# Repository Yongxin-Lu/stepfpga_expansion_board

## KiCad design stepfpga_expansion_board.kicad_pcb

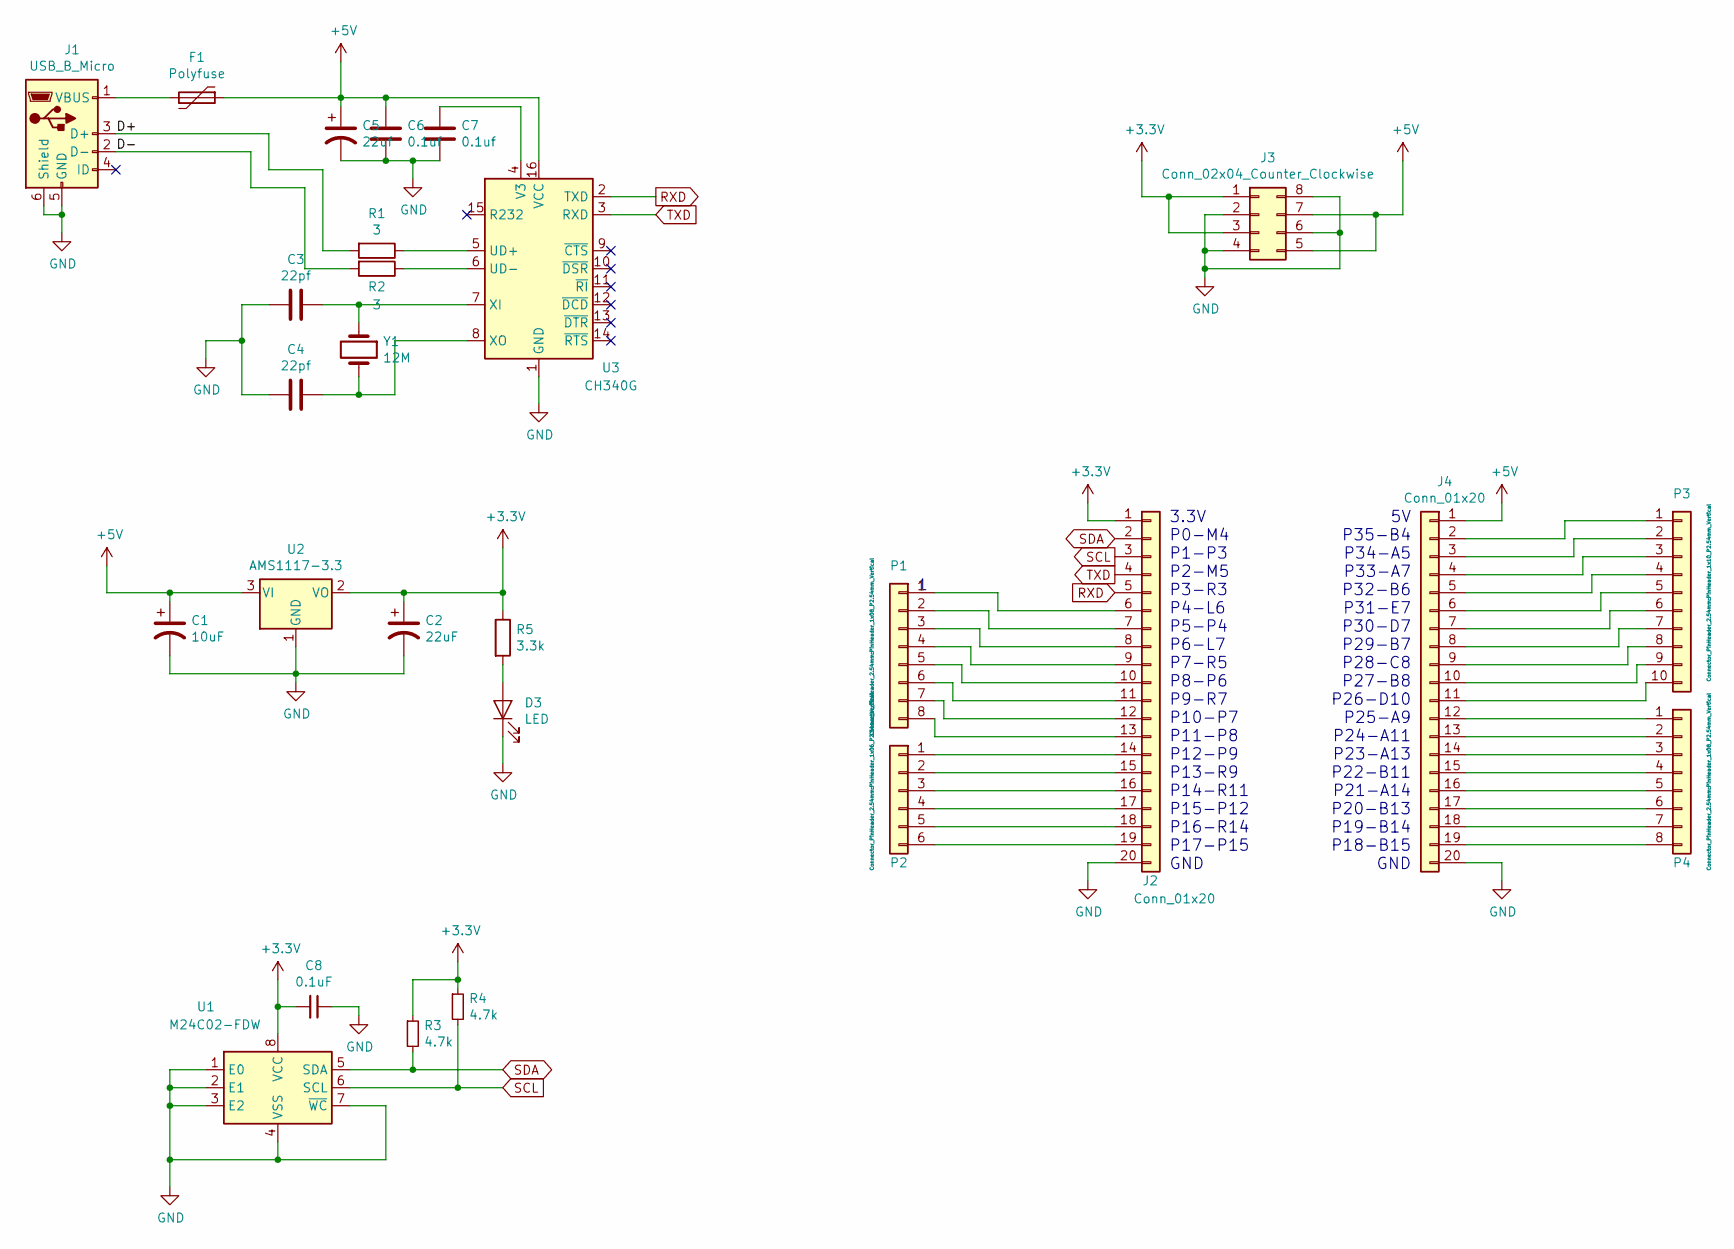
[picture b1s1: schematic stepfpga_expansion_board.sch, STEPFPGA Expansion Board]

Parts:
C1: 10uF; CP_EIA-3216-18_Kemet-A
C2: 22uF; CP_EIA-3216-18_Kemet-A
C3, C4: 22pf; C_0603_1608Metric
C5: 22uf; CP_EIA-3216-18_Kemet-A
C6, C7: 0.1uf; C_0603_1608Metric
C8: 0.1uF; C_0603_1608Metric
D3: LED; D_0603_1608Metric
F1: Polyfuse; Fuse_0805_2012Metric
J1: USB_B_Micro; USB_Micro-B_Molex_47346-0001
J2, J4: Conn_01x20; PinSocket_1x20_P2.54mm_Vertical
J3: Conn_02x04_Counter_Clockwise; PinHeader_2x04_P2.54mm_Vertical
P1: Power; PinHeader_1x08_P2.54mm_Vertical
P2: Analog; PinHeader_1x06_P2.54mm_Vertical
P3: Digital; PinHeader_1x10_P2.54mm_Vertical
P4: Digital; PinHeader_1x08_P2.54mm_Vertical
R1, R2: 3; R_0603_1608Metric
R3, R4: 4.7k; R_0603_1608Metric
R5: 3.3k; R_0603_1608Metric
U1: M24C02-FDW; TSSOP-8_4.4x3mm_P0.65mm
U2: AMS1117-3.3; SOT-223-3_TabPin2
U3: CH340G; SOIC-16_3.9x9.9mm_P1.27mm
Y1: 12M; HC49US

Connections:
+3V3: C2.1, C8.2, J2.1, J3.1, J3.3, R3.1, R4.1, R5.1, U1.8 (VCC), U2.2 (VO)
+5V: C1.1, C5.1, C6.1, F1.1, J3.5, J3.7, J4.1, U2.3 (VI), U3.16 (VCC)
/D+: J1.3 (D+), R1.2
/D-: J1.2 (D-), R2.2
GND: C1.2, C2.2, C3.2, C4.2, C5.2, C6.2, C7.2, C8.1, D3.1 (K), J1.5 (GND), J1.6 (Shield), J2.20, J3.2, J3.4, J3.6, J3.8, J4.20, U1.1 (E0), U1.2 (E1), U1.3 (E2), U1.4 (VSS), U1.7 (~WC), U2.1 (GND), U3.1 (GND)
unnamed: C3.1, U3.7 (XI), Y1.1
unnamed: C4.1, U3.8 (XO), Y1.2
unnamed: C7.1, U3.4 (V3)
unnamed: D3.2 (A), R5.2
unnamed: F1.2, J1.1 (VBUS)
unnamed: J2.6, P1.1
unnamed: J2.7, P1.2
unnamed: J2.8, P1.3
unnamed: J2.9, P1.4
unnamed: J2.10, P1.5
unnamed: J2.11, P1.6
unnamed: J2.12, P1.7
unnamed: J2.13, P1.8
unnamed: J2.14, P2.1
unnamed: J2.15, P2.2
unnamed: J2.16, P2.3
unnamed: J2.17, P2.4
unnamed: J2.18, P2.5
unnamed: J2.19, P2.6
unnamed: J4.2, P3.1
unnamed: J4.3, P3.2
unnamed: J4.4, P3.3
unnamed: J4.5, P3.4
unnamed: J4.6, P3.5
unnamed: J4.7, P3.6
unnamed: J4.8, P3.7
unnamed: J4.9, P3.8
unnamed: J4.10, P3.9
unnamed: J4.11, P3.10
unnamed: J4.12, P4.1
unnamed: J4.13, P4.2
unnamed: J4.14, P4.3
unnamed: J4.15, P4.4
unnamed: J4.16, P4.5
unnamed: J4.17, P4.6
unnamed: J4.18, P4.7
unnamed: J4.19, P4.8
unnamed: R1.1, U3.5 (UD+)
unnamed: R2.1, U3.6 (UD-)
RXD: J2.5, U3.2 (TXD)
SCL: J2.3, R4.2, U1.6 (SCL)
SDA: J2.2, R3.2, U1.5 (SDA)
TXD: J2.4, U3.3 (RXD)

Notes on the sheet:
3.3V P0-M4 P1-P3 P2-M5 P3-R3 P4-L6 P5-P4 P6-L7 P7-R5 P8-P6 P9-R7 P10-P7 P11-P8 P12-P9 P13-R9 P14-R11 P15-P12 P16-R14 P17-P15 GND
5V P35-B4 P34-A5 P33-A7 P32-B6 P31-E7 P30-D7 P29-B7 P28-C8 P27-B8 P26-D10 P25-A9 P24-A11 P23-A13 P22-B11 P21-A14 P20-B13 P19-B14 P18-B15 GND

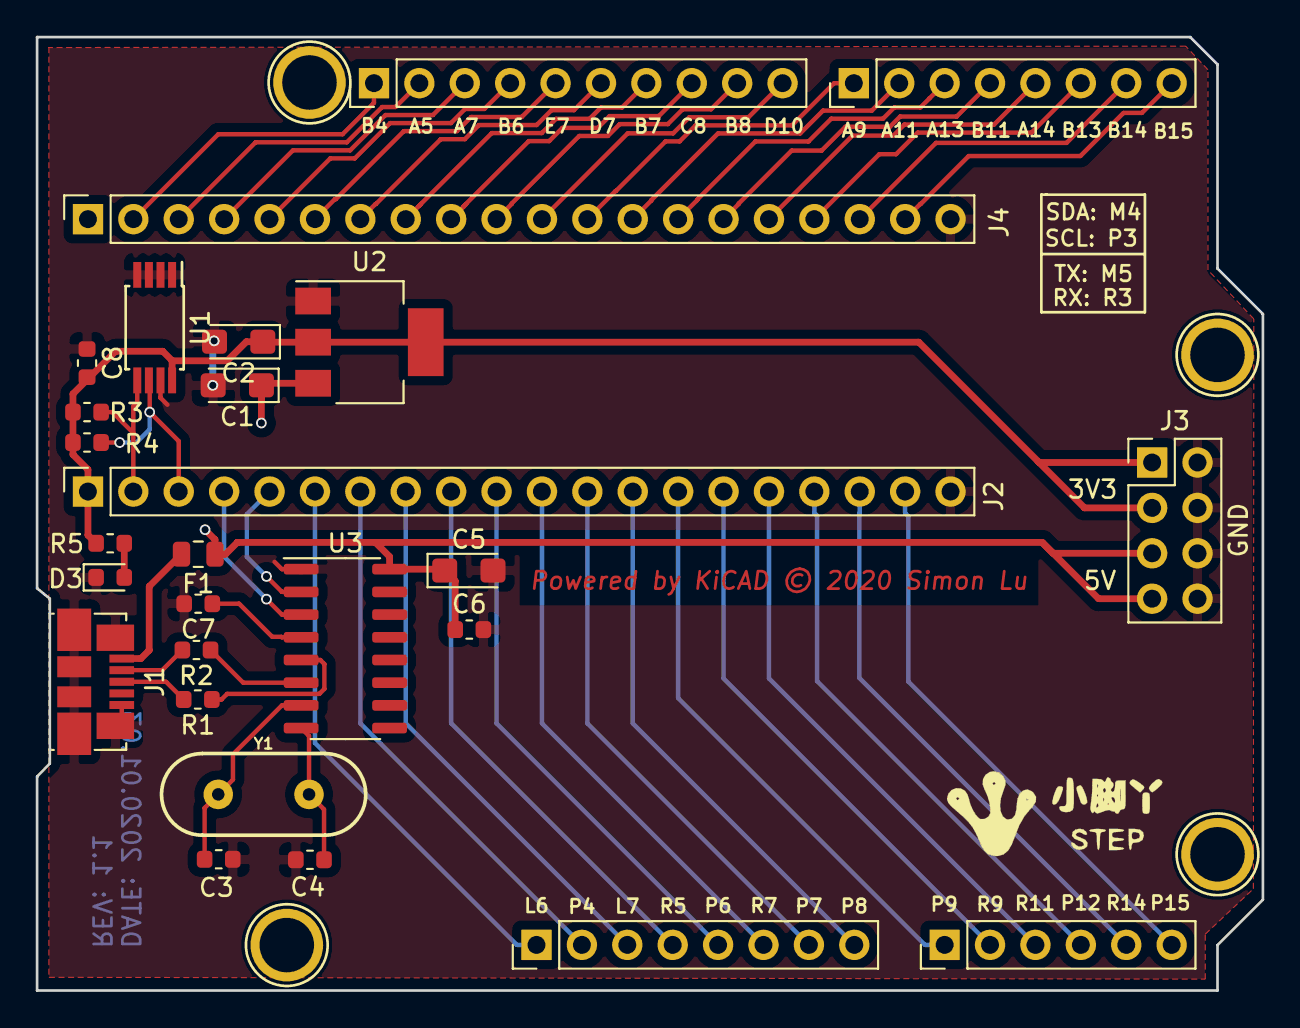
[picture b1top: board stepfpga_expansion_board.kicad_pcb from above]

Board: 2 copper layers, 68.6 x 53.3 mm, 31 parts (0 on the bottom side), 48 nets.

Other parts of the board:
P5, P6, P7, P8: CONN_01X01; Arduino_1pin

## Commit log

2020-02-29 demo
2020-02-29 demo2

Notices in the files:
stepfpga_expansion_board.kicad_pcb:
Powered by KiCAD © 2020 Simon Lu
